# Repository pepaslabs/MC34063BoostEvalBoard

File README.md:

# MC34063BoostEvalBoard
An evaluation board for use with the MC34063 switcher in boost configuration.

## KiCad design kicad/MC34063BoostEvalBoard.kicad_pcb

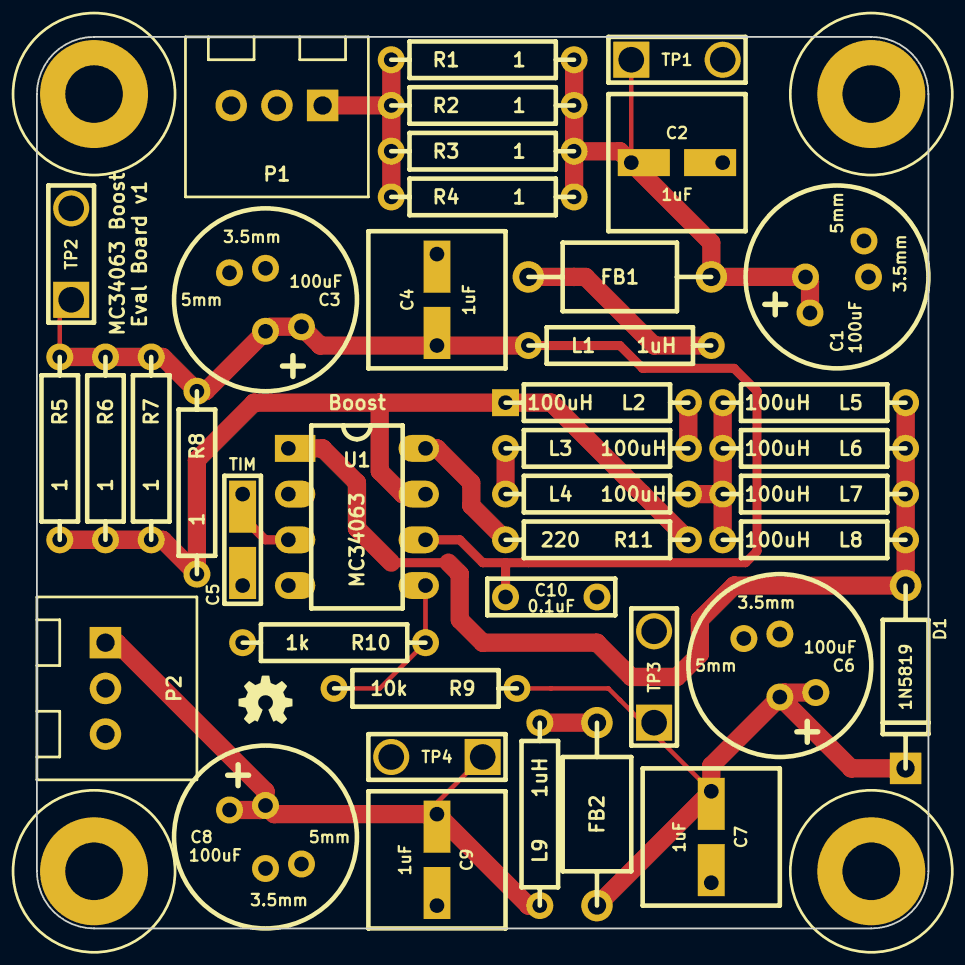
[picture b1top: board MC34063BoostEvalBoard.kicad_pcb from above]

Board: 2 copper layers, 49.5 x 49.5 mm, 44 parts (0 on the bottom side), 16 nets.

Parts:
C1, C3, C6, C8: 100uF; MedCap2
C2, C4, C7, C9: 1uF; ANYSSCAP_2_059B_0805
C5: TIM; CERCAP_2_059B_0805
C10: 0.1uF; CERCAP_2_059A
D1: 1N5819; DIODE_1A_069A_PL
FB1, FB2: FERRITE_BEAD; FERRITE_AXIAL_04_069A
H***: Val**; hole_M3
H***#2, H***#3, H***#4: Val**; hole_M3
L1, L9: 1uH; R_AXIAL_0W25_059A_PL
L2, L3, L4, L5, L6, L7, L8: 100uH; R_AXIAL_0W25_059A_PL
P1, P2: CONN_2; TERMINAL_BLOCK_2_5mm
R1, R2, R3, R4, R5, R6, R7, R8: 1; R_AXIAL_0W25_059A_PL
R9: 10k; R_AXIAL_0W25_059A_PL
R10: 1k; R_AXIAL_0W25_059A_PL
R11: 220; R_AXIAL_0W25_059A_PL
TP1, TP2, TP3, TP4: TEST; TEST_2
U1: MC34063; DIP8_059Bi_PL

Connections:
GND: C1.2, C2.2, C3.2, C4.2, C5.2, C6.2, C7.2, C8.2, C9.2, C10.2, P1.2, P2.2, R10.2, TP1.2, TP2.2, TP3.2, TP4.2, U1.2, U1.4
unnamed: L2.1, L3.2
unnamed: L3.1, L4.1
unnamed: FB1.2, L1.2
unnamed: FB2.2, L9.2
unnamed: C6.1, C7.1, D1.2, FB2.1, R9.1, TP3.1
unnamed: R11.2, U1.8
unnamed: L4.2, L5.2, L6.2, L7.2, L8.2
unnamed: D1.1, L5.1, L6.1, L7.1, L8.1, U1.1
unnamed: L2.2, R5.2, R6.2, R7.2, R8.2, R11.1, U1.7
unnamed: C5.1, U1.3
unnamed: R9.2, R10.1, U1.5
unnamed: C3.1, C4.1, C10.1, L1.1, R5.1, R6.1, R7.1, R8.1, TP2.1, U1.6
unnamed: C1.1, C2.1, FB1.1, R1.2, R2.2, R3.2, R4.2, TP1.1
unnamed: C8.1, C9.1, L9.1, P2.1, TP4.1
Vin: P1.1, R1.1, R2.1, R3.1, R4.1

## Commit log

2015-05-10 adding board shots
